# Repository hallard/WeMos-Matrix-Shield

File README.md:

# Basic ESP8266 WeMos Matrix Shield for Digital Morphing Clock

**This project has been deprecated** please check new version with ESP32 and DMA version [here](https://github.com/hallard/WeMos-Matrix-Shield-DMA)

This shield is used to get simplify ESP8266 connectivity with a [WeMos][22] ESP8266 and nice matric RGB led. This idea came from excellent project called [Morphing Digital Clock][3] done by [HariFun][1] Instructable

See it in action, nice isn't it?

**Pay attention V1.2 got a missing trace between Input and Output connector G1**
See Issue [#2](https://github.com/hallard/WeMos-Matrix-Shield/issues/2). and how to fix. If you have V1.2 don't forget to solder a wire between these 2 points (see below). Thanks to nthonyjclarke and dragondaud for pointing this out

This breakout has just few minimal features.

**New in V1.6**

- added experimetal support for ESP32 boards with WeMos Mini D1 wiring called ESP32 Mini Kit or ESP32 Wemos, or ESP32 MH-ET Live such as this [banggood model](https://www.banggood.com/Wemos-D1-Mini-ESP32-ESP-32-WiFiBluetooth-Internet-Of-Things-Development-Board-Based-ESP8266-p-1205854.html) or this [aliexpress](https://www.aliexpress.com/item/MH-ET-LIVE-D1-mini-ESP32-ESP-32-WiFi-Bluetooth-Internet-of-Things-development-board-based/32815530502.html). But you can find a lot also on ebay, not a problem.
- PCB board has been extented to fit this ESP32 Mini module but also backward compatible with WeMos Mini D1 ESP8266.

Please check wiring and picture before ordering, should looks like something like that:

**New in V1.5**

- changed power connector spacing to fit the same than Matrix one's [#4](https://github.com/hallard/WeMos-Matrix-Shield/issues/4)
- added space for smaller Matrix power connector [#4](https://github.com/hallard/WeMos-Matrix-Shield/issues/4)
- generated [gerbers files](https://github.com/hallard/WeMos-Matrix-Shield/master/gerbers/)

**New in V1.4**

- Added DS18B20 footprint + 4K7 PullUp resistor (DS18B20 DQ connected to GPIO0/D3)
- Removed E connection to add DS18B20 (DQ PIN), added solder jumper if needed this connection back.
- added space for barrel DC connector if connector input connector is top soldered see [#3](https://github.com/hallard/WeMos-Matrix-Shield/issues/3)
- Changed LDR orientation

**New in V1.3**

- Fixed missing trace missing beetwen Input and Output connector G1. That was cutted by accident when creating V1.2 from V1.1.

**New in V1.2**

- Added footprint for a Photoresistor (LDR) + Resistor to be able to adjust luminosity with ambiant light
- This version has a missing trace between Input G0 and Output G1, connect a wire has follow to fix

**New in V1.1**

- Power, added big connector 3.5mm spaced to put the supplied power cable
- Changed 3.5mm Phoenix connector by a 5mm one allowing the stronger power cable to fit info
- Moved output connector to the right you can use the supplied flat band connector
- Output connector can go straight to output connector of Matrix, allowing to use a 6 PIN ISP Arduino Like ribbon cable.
- Increased PCB traces width for 5V power
- Added some wiring info on bottom silk

**Still in V1.0+**

- DC Barrel power connector 
- Zero Press Fit power connector
- All necessary headers to connect the Matric Shield

WeMos provide 3 D1, [D1 Mini Lite][20], [D1 Mini][21] or [D1 Mini Pro][22].

**V1.0 boards are tested and working**. But it was missing B1 on 6 pin out connector, so you should grab it elsewhere, but it's now fixed on V1.1+ and also aligned out connector pins to the needed Matrix Order. You can order boards V1.4 at [PCBs.io][4]

# Detailed Description

Look at the schematics for more informations.

# Schematic  

# Boards  

&nbsp;

You can order the PCB of this board at [PCBs.io][4]. PCBs.io give me some reward when you order my designed boards from their site. This is pretty good, because I can use these rewards to create and design new boards and order them for free, so if you don't care about PCB manufacturer please use PCBs.io.

# Firmware

I suggest to use the excellent code done by [dragondaud](https://github.com/dragondaud/myClock), it has all I wanted to do and mandatory feature, OTA and LDR Luminosity management.

# Assembled boards

Board have been made to be plugged directly on the matrix shield, see picture below:

Theese are pictures of the 1st PCB V1.0 with LDR Live Fix, just to see how are connected wire, I'm waiting new boards (V1.3), to take new pictures and show easier connecting.

**2x8 pins female connector is soldered on the bottom side of PCB**

**On this one you can see latest version with ESP32 MH-ET Live**

# BOM

Nothing fancy, just some headers and 2 differents power conector (choose the one you prefer) :

 - Ebay search for "DC Power Jack Barrel PCB Mount"
 
 - Phoenix contact PCB terminal block - SPTAF ref 1864286 (V1.0) or 1864435 (V1.1+) can be found anywhere
 
- Ebay search for "2X8 Pin 2.54mm Double Row Female Header" or polulu product #1028, you can also use twice 1x8 pin female or even twice 2x4 pins female, plenty of option for this one

# License

This work is licensed under a [Creative Commons Attribution-NonCommercial-ShareAlike 4.0 International License](https://creativecommons.org/licenses/by-nc-sa/4.0/)    

# Misc

See news and other projects on my [blog][2] 

Thanks to [HariFun][1] for this awesome stuff, please review and see how to build on [Instructable][3]
 
[1]: https://www.instructables.com/member/HariFun/
[2]: https://hallard.me
[3]: https://www.instructables.com/id/Morphing-Digital-Clock/
[4]: https://PCBs.io/share/rG9w7

[20]: https://wiki.wemos.cc/products:d1:d1_mini_lite
[21]: https://wiki.wemos.cc/products:d1:d1_mini
[22]: https://wiki.wemos.cc/products:d1:d1_mini_pro

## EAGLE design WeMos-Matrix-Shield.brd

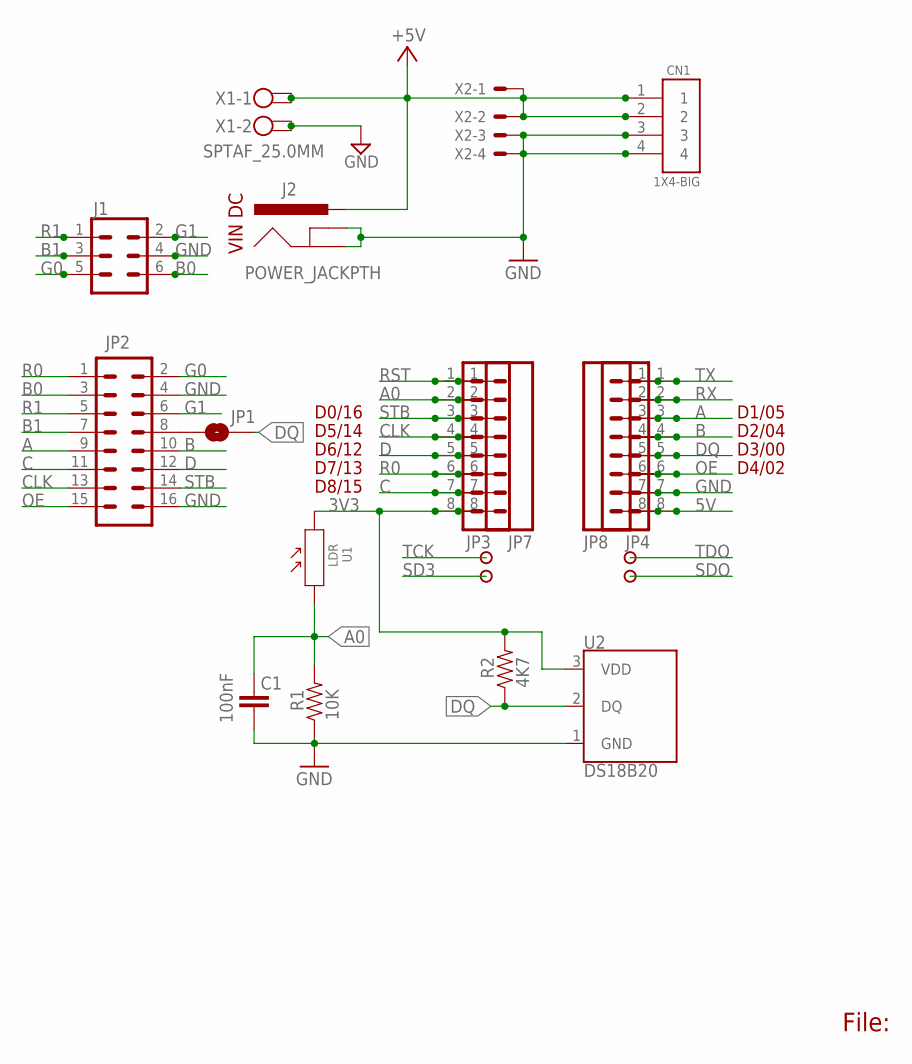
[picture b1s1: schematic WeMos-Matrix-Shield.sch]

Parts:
C1: 100nF; CAP-PTH-SMALL2
CN1: 1X4-BIG; 1X04-BIG
J1: CONN_03X22X3_SILK_MALE_PTH; 2X3
J2: POWER_JACKPTH; POWER_JACK_PTH
JP1: JUMPER-SMT_2_NO_NO-SILK; SMT-JUMPER_2_NO_NO-SILK
JP2: M08X2; 2X8
JP3, JP4, JP7, JP8: M08NO_SILK_FEMALE_PTH; 1X08_NO_SILK
R1: 10K; 1/6W-RES
R2: 4K7; 1/6W-RES
U1: LDR; SNR2-3.0
U2: DS18B20; TO-92-AMMO
VIN1, VIN2, VIN3, VIN4: PADNORMAL; PAD
X1: SPTAF_25.0MM; SPTAF_2X50
X2: KK-156-4

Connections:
3V3: JP3.8, JP7.8, R2.2, U1.2, U2.3 (VDD)
5V: CN1.1, CN1.2, J2.PWR, JP4.8, JP8.8, X1.1, X1.1A (2), X2.1, X2.2
A: JP2.9, JP4.3, JP8.3
A0: C1.1, JP3.2, JP7.2, R1.2, U1.1
B: JP2.10, JP4.4, JP8.4
B0: J1.6, JP2.3
B1: J1.3, JP2.7
C: JP2.11, JP3.7, JP7.7
CLK: JP2.13, JP3.4, JP7.4
D: JP2.12, JP3.5, JP7.5
DQ: JP1.2, JP4.5, JP8.5, R2.1, U2.2 (DQ)
G0: J1.5, JP2.2
G1: J1.2, JP2.6
GND: C1.2, CN1.3, CN1.4, J1.4, J2.GND, J2.GNDBREAK, JP2.4, JP2.16, JP4.7, JP8.7, R1.1, U2.1 (GND), X1.2 (1), X1.2A (2), X2.3, X2.4
unnamed: JP1.1, JP2.8
OE: JP2.15, JP4.6, JP8.6
R0: JP2.1, JP3.6, JP7.6
R1: J1.1, JP2.5
RST: JP3.1, JP7.1
RX: JP4.2, JP8.2
SD3: VIN4.1
SDO: VIN2.1
STB: JP2.14, JP3.3, JP7.3
TCK: VIN3.1
TDO: VIN1.1
TX: JP4.1, JP8.1

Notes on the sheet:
File:
D4/02
D3/00
D6/12
D2/04
D1/05
D7/13
D5/14
D8/15
D0/16
VIN DC

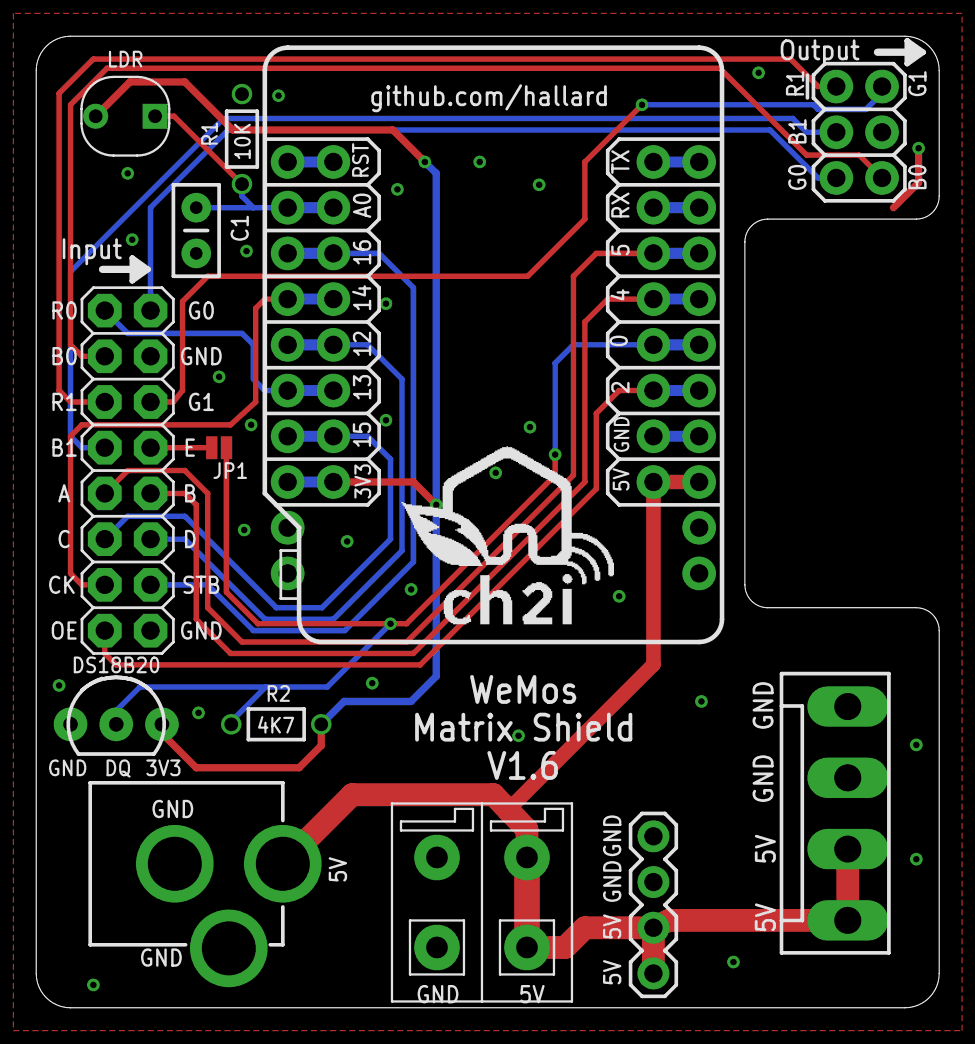
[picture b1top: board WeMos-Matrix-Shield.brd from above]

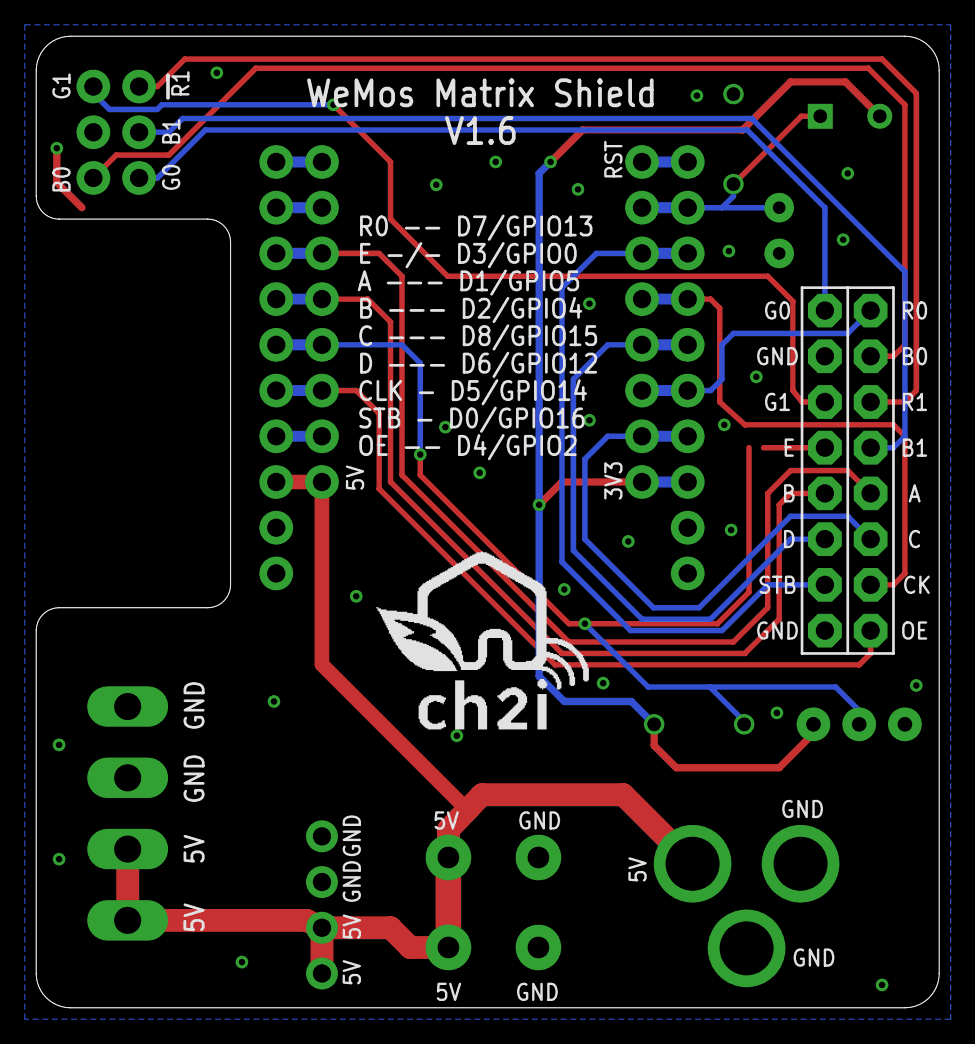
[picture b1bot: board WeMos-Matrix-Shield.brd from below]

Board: 2 copper layers, 50.2 x 54.0 mm, 22 parts (5 on the bottom side), 22 nets.

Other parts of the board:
U$1, U$3: LOGO_CH2I_110MM

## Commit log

2018-09-01 :space_invader: Added .gitattributes
2018-09-01 Creation
2018-09-01 fixed misnamed
2018-09-01 Added picture
2018-09-01 Fix Picture link
2018-09-01 Changed Title
2018-09-09 Bump to V1.1
2018-09-09 Cosmetic
2018-09-15 Fixed PCBs.io link
2018-10-06 Updated to V1.3
2018-10-06 Added dragondaud firmware link
2018-10-21 Added mounting pictures
2018-10-21 Added descriptions
2018-10-21 Added 2x8 pin connector on BOM
2018-10-21 reduced image size
2018-10-21 Added connector picture
2018-10-21 Updated to V1.4
2018-10-26 Updated to V1.5
2018-10-26 typo
2018-10-31 Typo between D7/D3 for DQ pin
2018-11-05 V1.6 Gerbers
2018-11-05 Updated to V1.6
2018-11-29 ESP32 Version
2021-02-27 Update README.md
    Added link to now project version
2026-04-29 Switch to CC BY-NC-SA 4.0 license, add LICENSE file

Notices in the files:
parts and their libraries:
SparkFun-Connectors: Licensing: Creative Commons ShareAlike 4.0 International - https://creativecommons.org/licenses/by-sa/4.0
PatternAgents-ProtoPads: License : http://creativecommons.org/licenses/by-sa/4.0
(Creative Commons 4.0)
